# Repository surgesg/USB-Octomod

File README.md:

# USB-Octomod

The USB-Octomod is a USB device which allows generation of computer-controlled analog synthesizer control voltages
in the range of approximately +/- 5V.
Using a small open-source and cross-platform host application, the user is able to control the 8 output channels
of the Octomod through a simple OSC/MIDI interface. 
The OSC interface allows composers, musicians, etc. to control the Octomod from their software environment of choice.

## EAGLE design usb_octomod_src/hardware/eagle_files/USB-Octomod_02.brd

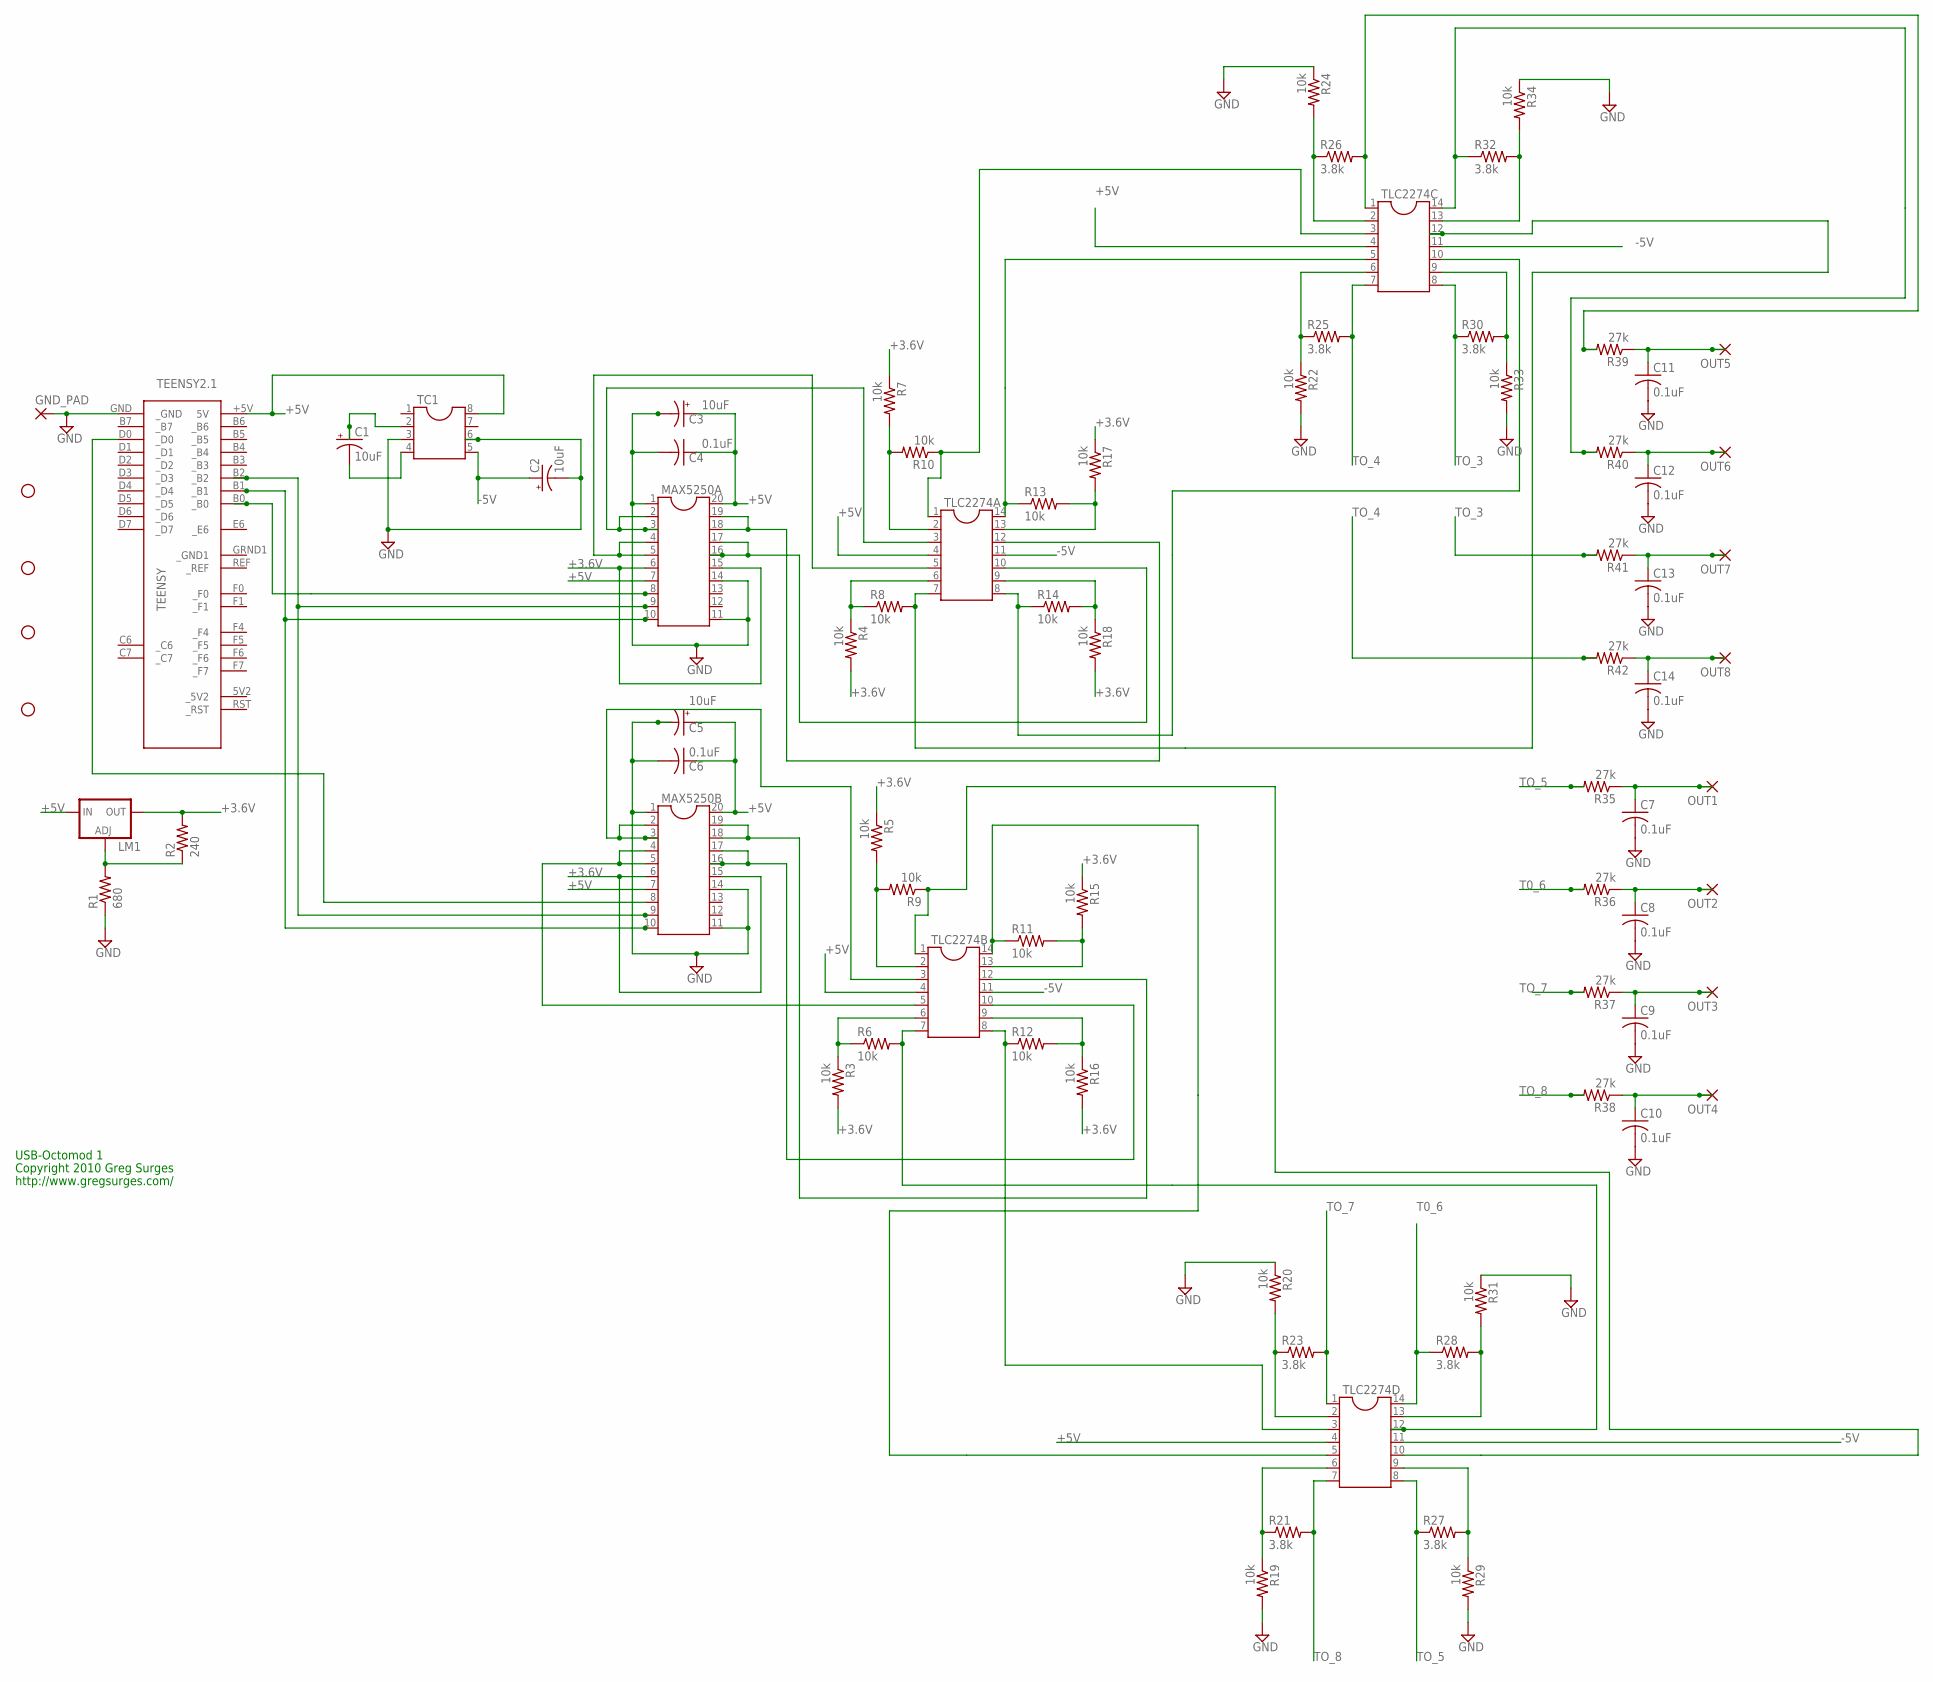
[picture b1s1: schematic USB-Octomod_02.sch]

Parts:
C1, C2, C3, C5: 10uF; E2,5-6
C4, C6, C7, C8, C9, C10, C11, C12, C13, C14: 0.1uF; C025-040X050
GND_PAD: 2,15/1,0
JP1, JP2, JP3, JP4: STAND-OFF
LM1: LM317TL; 317TL
MAX5250A, MAX5250B: DIL20
OUT1, OUT2, OUT3, OUT4, OUT5, OUT6, OUT7, OUT8: 2,15/1,0
R1: 680; 0207/10
R2: 240; 0207/10
R3, R4, R5, R6, R7, R8, R9, R10, R11, R12, R13, R14, R15, R16, R17, R18, R19, R20, R22, R24, R29, R31, R33, R34: 10k; 0207/10
R21, R23, R25, R26, R27, R28, R30, R32: 3.8k; 0207/10
R35, R36, R37, R38, R39, R40, R41, R42: 27k; 0207/10
TC1: DIL8; DIL08
TEENSY2.1: TEENSY
TLC2274A, TLC2274B, TLC2274C, TLC2274D: DIL14

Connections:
+3.6V: LM1.2 (OUT), MAX5250A.6, MAX5250A.15, MAX5250B.6, MAX5250B.15, R2.2, R3.2, R4.2, R5.1, R7.1, R15.1, R16.2, R17.1, R18.2
+5V: C3.+, C4.1, C5.+, C6.1, LM1.3 (IN), MAX5250A.7, MAX5250A.20, MAX5250B.7, MAX5250B.20, TC1.8, TEENSY2.1.+5V (5V), TLC2274A.4, TLC2274B.4, TLC2274C.4, TLC2274D.4
-5V: C2.+, TC1.5, TLC2274A.11, TLC2274B.11, TLC2274C.11, TLC2274D.11
GND: C2.-, C3.-, C4.2, C5.-, C6.2, C7.2, C8.2, C9.2, C10.2, C11.2, C12.2, C13.2, C14.2, GND_PAD.1, MAX5250A.1, MAX5250A.11, MAX5250A.14, MAX5250B.1, MAX5250B.11, MAX5250B.14, R1.1, R19.2, R20.1, R22.2, R24.1, R29.2, R31.1, R33.2, R34.1, TC1.3, TC1.6, TEENSY2.1.GND (_GND)
unnamed: MAX5250A.8, TEENSY2.1.B0 (_B0)
unnamed: MAX5250A.10, MAX5250B.10, TEENSY2.1.B1 (_B1)
unnamed: MAX5250A.9, MAX5250B.9, TEENSY2.1.B2 (_B2)
unnamed: C1.+, TC1.2
unnamed: R10.1, TLC2274A.1, TLC2274C.3
unnamed: LM1.1 (ADJ), R1.2, R2.1
unnamed: C1.-, TC1.4
unnamed: R7.2, R10.2, TLC2274A.2
unnamed: C11.1, OUT5.1, R39.1
unnamed: R4.1, R8.1, TLC2274A.6
unnamed: R13.2, R17.2, TLC2274A.13
unnamed: C12.1, OUT6.1, R40.1
unnamed: C13.1, OUT7.1, R41.1
unnamed: C14.1, OUT8.1, R42.1
unnamed: R5.2, R9.2, TLC2274B.2
unnamed: C7.1, OUT1.1, R35.1
unnamed: R3.1, R6.1, TLC2274B.6
unnamed: C8.1, OUT2.1, R36.1
unnamed: C9.1, OUT3.1, R37.1
unnamed: R11.2, R15.2, TLC2274B.13
unnamed: C10.1, OUT4.1, R38.1
unnamed: R14.2, R18.1, TLC2274A.9
unnamed: R12.2, R16.1, TLC2274B.9
unnamed: MAX5250B.8, TEENSY2.1.D0 (_D0)
unnamed: R24.2, R26.1, TLC2274C.2
unnamed: R26.2, R39.2, TLC2274C.1
unnamed: R32.2, R34.2, TLC2274C.13
unnamed: R32.1, R40.2, TLC2274C.14
unnamed: R22.1, R25.1, TLC2274C.6
unnamed: R30.2, R33.1, TLC2274C.9
unnamed: R20.2, R23.1, TLC2274D.2
unnamed: R28.2, R31.2, TLC2274D.13
unnamed: R19.1, R21.1, TLC2274D.6
unnamed: R27.2, R29.1, TLC2274D.9
OUT2: R8.2, TLC2274A.7, TLC2274C.12
OUT3: R14.1, TLC2274A.8, TLC2274C.10
OUT4: R13.1, TLC2274A.14, TLC2274C.5
OUT6: R11.1, TLC2274B.14, TLC2274D.5
OUT8: R9.1, TLC2274B.1, TLC2274D.10
OUTA1: MAX5250A.2, MAX5250A.3, TLC2274A.3
OUTA2: MAX5250A.4, MAX5250A.5, TLC2274A.5
OUTA3: MAX5250A.18, MAX5250A.19, TLC2274A.12
OUTA4: MAX5250A.16, MAX5250A.17, TLC2274A.10
OUTB1: MAX5250B.2, MAX5250B.3, TLC2274B.3
OUTB2: MAX5250B.4, MAX5250B.5, TLC2274B.5
OUTB3: MAX5250B.18, MAX5250B.19, TLC2274B.12
OUTB4: MAX5250B.16, MAX5250B.17, TLC2274B.10
T0_6: R28.1, R36.2, TLC2274D.14
TO_3: R30.1, R41.2, TLC2274C.8
TO_4: R25.2, R42.2, TLC2274C.7
TO_5: R27.1, R35.2, TLC2274D.8
TO_7: R23.2, R37.2, TLC2274D.1
TO_8: R21.2, R38.2, TLC2274D.7
TT3: R12.1, TLC2274B.8, TLC2274D.3
TTT: R6.2, TLC2274B.7, TLC2274D.12

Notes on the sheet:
USB-Octomod 1
Copyright 2010 Greg Surges
http://www.gregsurges.com/

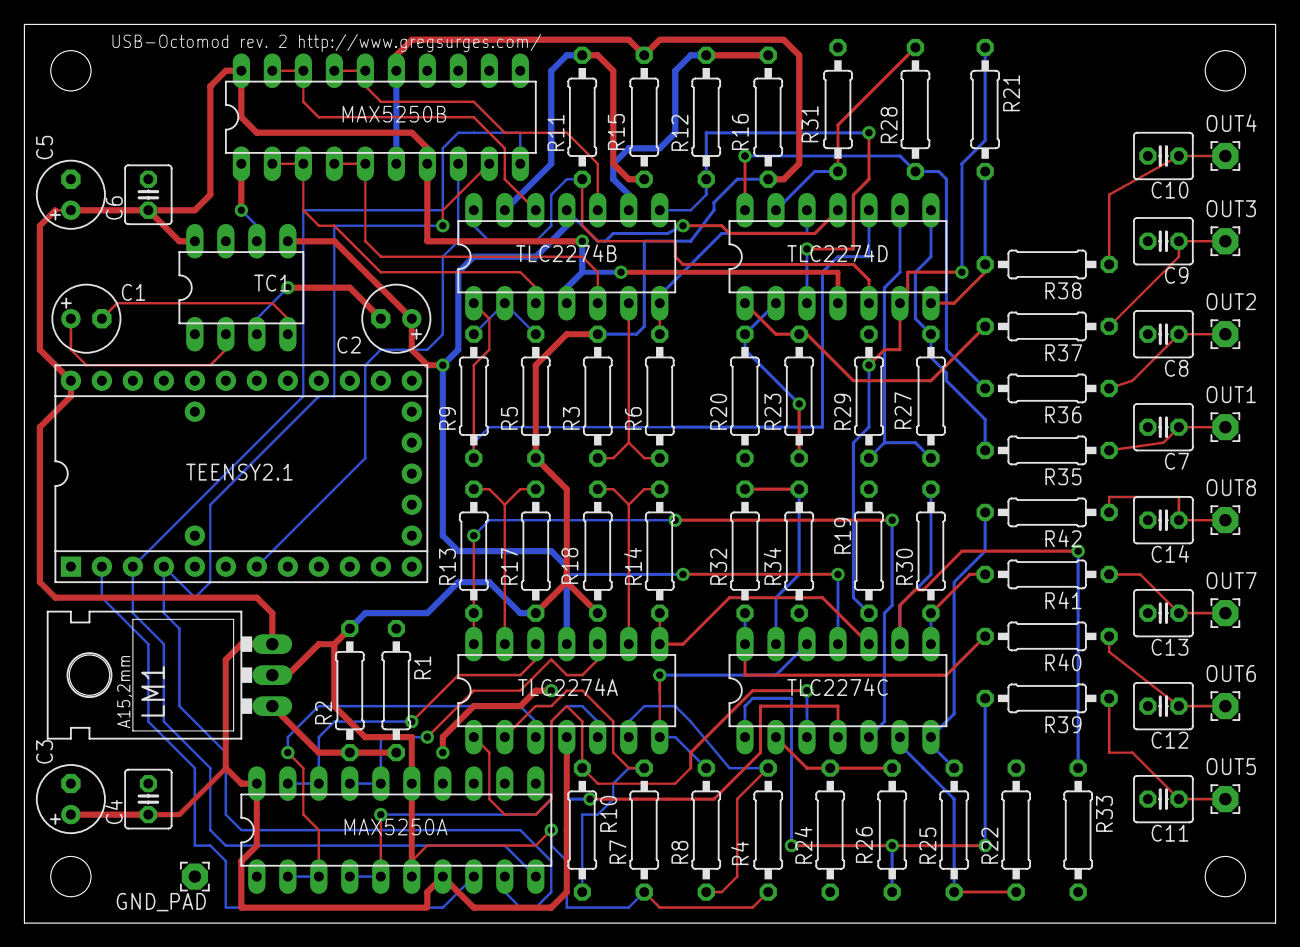
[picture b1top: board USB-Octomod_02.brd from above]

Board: 2 copper layers, 102.5 x 73.7 mm, 78 parts (0 on the bottom side), 59 nets.

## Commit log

2016-03-27 removed old svn cruft
2016-07-05 restructuring
2016-07-05 added GPL
2016-07-05 added .brd file
2016-07-05 added .sch file
2016-07-05 added schematic pdf file
